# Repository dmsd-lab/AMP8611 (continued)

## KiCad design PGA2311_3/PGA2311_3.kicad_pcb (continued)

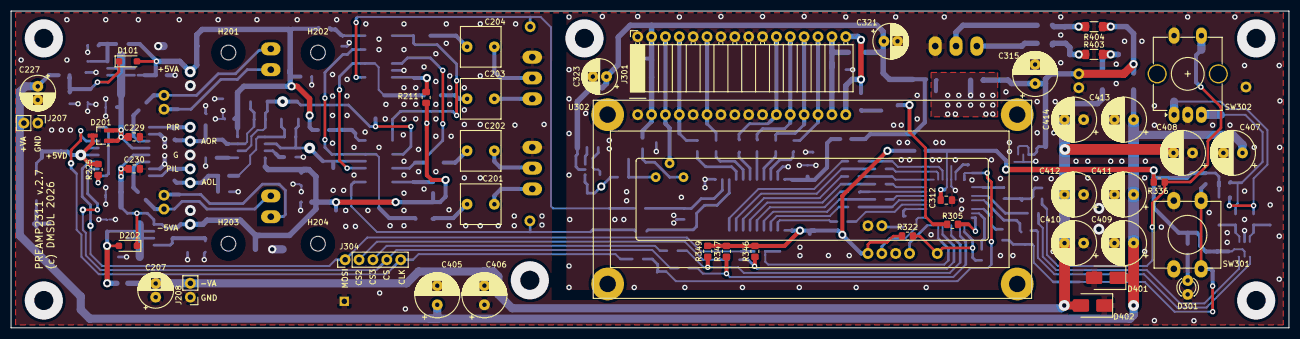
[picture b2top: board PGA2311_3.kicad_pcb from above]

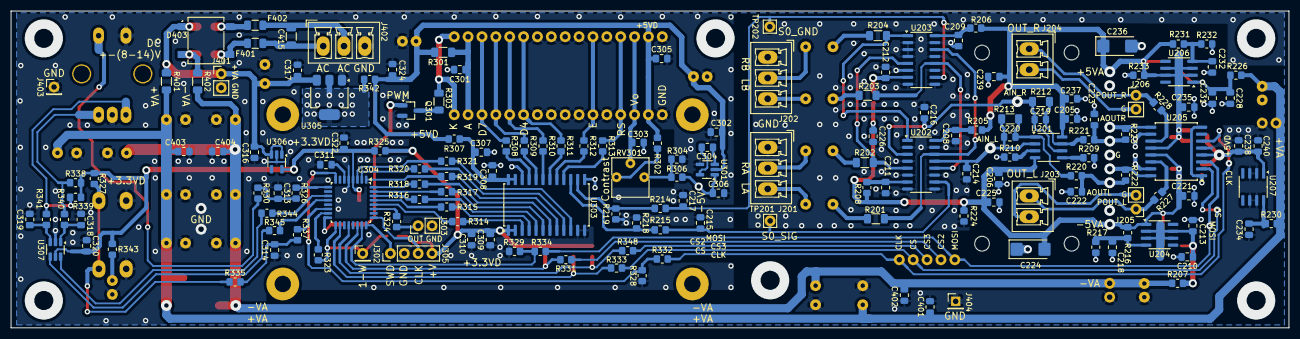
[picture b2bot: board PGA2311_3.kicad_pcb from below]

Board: 2 copper layers, 234.0 x 58.0 mm, 213 parts (164 on the bottom side), 128 nets.

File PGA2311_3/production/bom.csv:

Designator,Footprint,Quantity,Value,LCSC Part #
"C201, C202, C203, C204",C_Rect_L7.2mm_W7.2mm_P5.00mm_FKS2_FKP2_MKS2_MKP2,4,1.5u,
"C205, C206, C208, C209, C211, C212, C221, C225, C226, C229, C230, C235, C237, C238, C239, C303, C309, C310, C311, C312, C313, C314, C318, C319, C320",0805,25,100n,
"C207, C227, C321, C323",CP_Radial_D6.3mm_P2.50mm,4,100u,
"C210, C218, C228, C232, C234, C240, C301, C302, C304, C305, C306, C307, C308, C316, C317, C322, C324, C401, C402, C403, C404",0805,21,10u,
"C213, C214, C216, C231, R207, R222, R223, R226, R230, R304, R325",0805,11,0,
"C215, C217",0805,2,220p,
"C219, C220",0805,2,33p,
"C222, C223",0805,2,1n,
"C224, C236",CP_EIA-6032-20_AVX-F_HandSolder,2,33u,
"C315, C405, C406, C407, C408, C409, C410, C411, C412, C413, C414",CP_Radial_D8.0mm_P3.50mm,11,220u,
C415,1206,1,100n,
"D101, D202",D_SOD-123,2,1N5819,
D201,SOT-23_Handsoldering,1,BAS40-04,
D301,LED_D3.0mm,1,LED_GREEN,
"D401, D402",D_SMB,2,SMAJ15.0A,
D403,Diode_Bridge_OnSemi_SDIP-4L,1,DF01S,
"F401, F402",1206,2,MF-NSMF012-2,
"J201, J202, J402","PhoenixContact_MCV_1,5_3-G-3.81_1x03_P3.81mm_Vertical",3,3,
"J203, J204","PhoenixContact_MCV_1,5_2-G-3.81_1x02_P3.81mm_Vertical",2,2,
"J205, J206, J207, J208",PinHeader_1x02_P2.54mm_Vertical,4,2,
J301,PinSocket_1x16_P2.54mm_Horizontal,1,Conn_01x16,
"J302, J403, J404",PinHeader_1x01_P2.54mm_Vertical,3,1,
J303,PinHeader_1x02_P2.54mm_Vertical,1,Conn_01x02,
J304,PinHeader_1x05_P2.54mm_Vertical,1,4,
J305,PinHeader_1x04_P2.54mm_Vertical,1,4,
J401,PinHeader_1x02_P2.54mm_Vertical,1,1,
Q301,SOT-23_Handsoldering,1,BC817-40,
"R201, R202, R203, R204, R212, R213",1206,6,10k 1%,
"R205, R206, R227, R228, R308, R309, R310, R311, R312, R313, R314, R315, R316, R317, R318, R319, R320, R321",0805,18,100,
"R208, R211",0805,2,10,
"R209, R210",0805,2,5.1k,
"R214, R215, R224, R233, R323, R326, R327, R331, R332, R333, R334, R336, R337, R338, R339, R344, R345, R348",0805,18,1k,
"R216, R231",0805,2,330 1%,
"R217, R232",0805,2,1k 1%,
"R218, R219, R225, R328, R329, R330, R335, R340, R341, R346, R347, R349",0805,12,10k,
"R220, R221, R343",0805,3,220,
"R301, R401, R402",1206,3,1,
"R302, R306",0805,2,2.7k,
R303,1206,1,100,
"R305, R322, R324",0805,3,"2,7k",
"R307, R342",0805,2,0.33,
"R403, R404",1206,2,0,
RV301,Potentiometer_Vishay_T73YP_Vertical,1,KLS4-3362P 5.1k,
SW301,SW_PUSH-12mm,1,SW_Push,
SW302,RotaryEncoder_Alps_EC12E-Switch_Vertical_H20mm_CircularMountingHoles,1,Encoder PEC11R,
"TP201, TP202",TestPoint_THTPad_2.0x2.0mm_Drill1.0mm,2,TestPoint,
U201,SOIC-8_3.9x4.9mm_P1.27mm,1,OPA1678IDR,
"U202, U203",SOIC-16_3.9x9.9mm_P1.27mm,2,CD74HCT4052,
U204,SOIC-8_3.9x4.9mm_P1.27mm,1,LM337LM,
U205,SOIC-16W_7.5x10.3mm_P1.27mm,1,PGA2311UA,
U206,SOIC-8_3.9x4.9mm_P1.27mm,1,LM317LIDR,
U207,SOIC-8_3.9x4.9mm_P1.27mm,1,UA78L05AIDR,
U301,SOT-23-5_HandSoldering,1,TPS60403DBV,
U302,WC1602A,1,WH1602B,
U303,SOIC-24W_7.5x15.4mm_P1.27mm,1,SN74LVC8T245DW,
U304,LQFP-32_7x7mm_P0.8mm,1,STM32G070KBT6,
U305,SOT-223-3_TabPin2,1,TLV1117-50IDC,
U306,SOT-23-5_HandSoldering,1,LP2985-33DBV,
U307,SOT-23-6_Handsoldering,1,SN74LVC2G17DBV,

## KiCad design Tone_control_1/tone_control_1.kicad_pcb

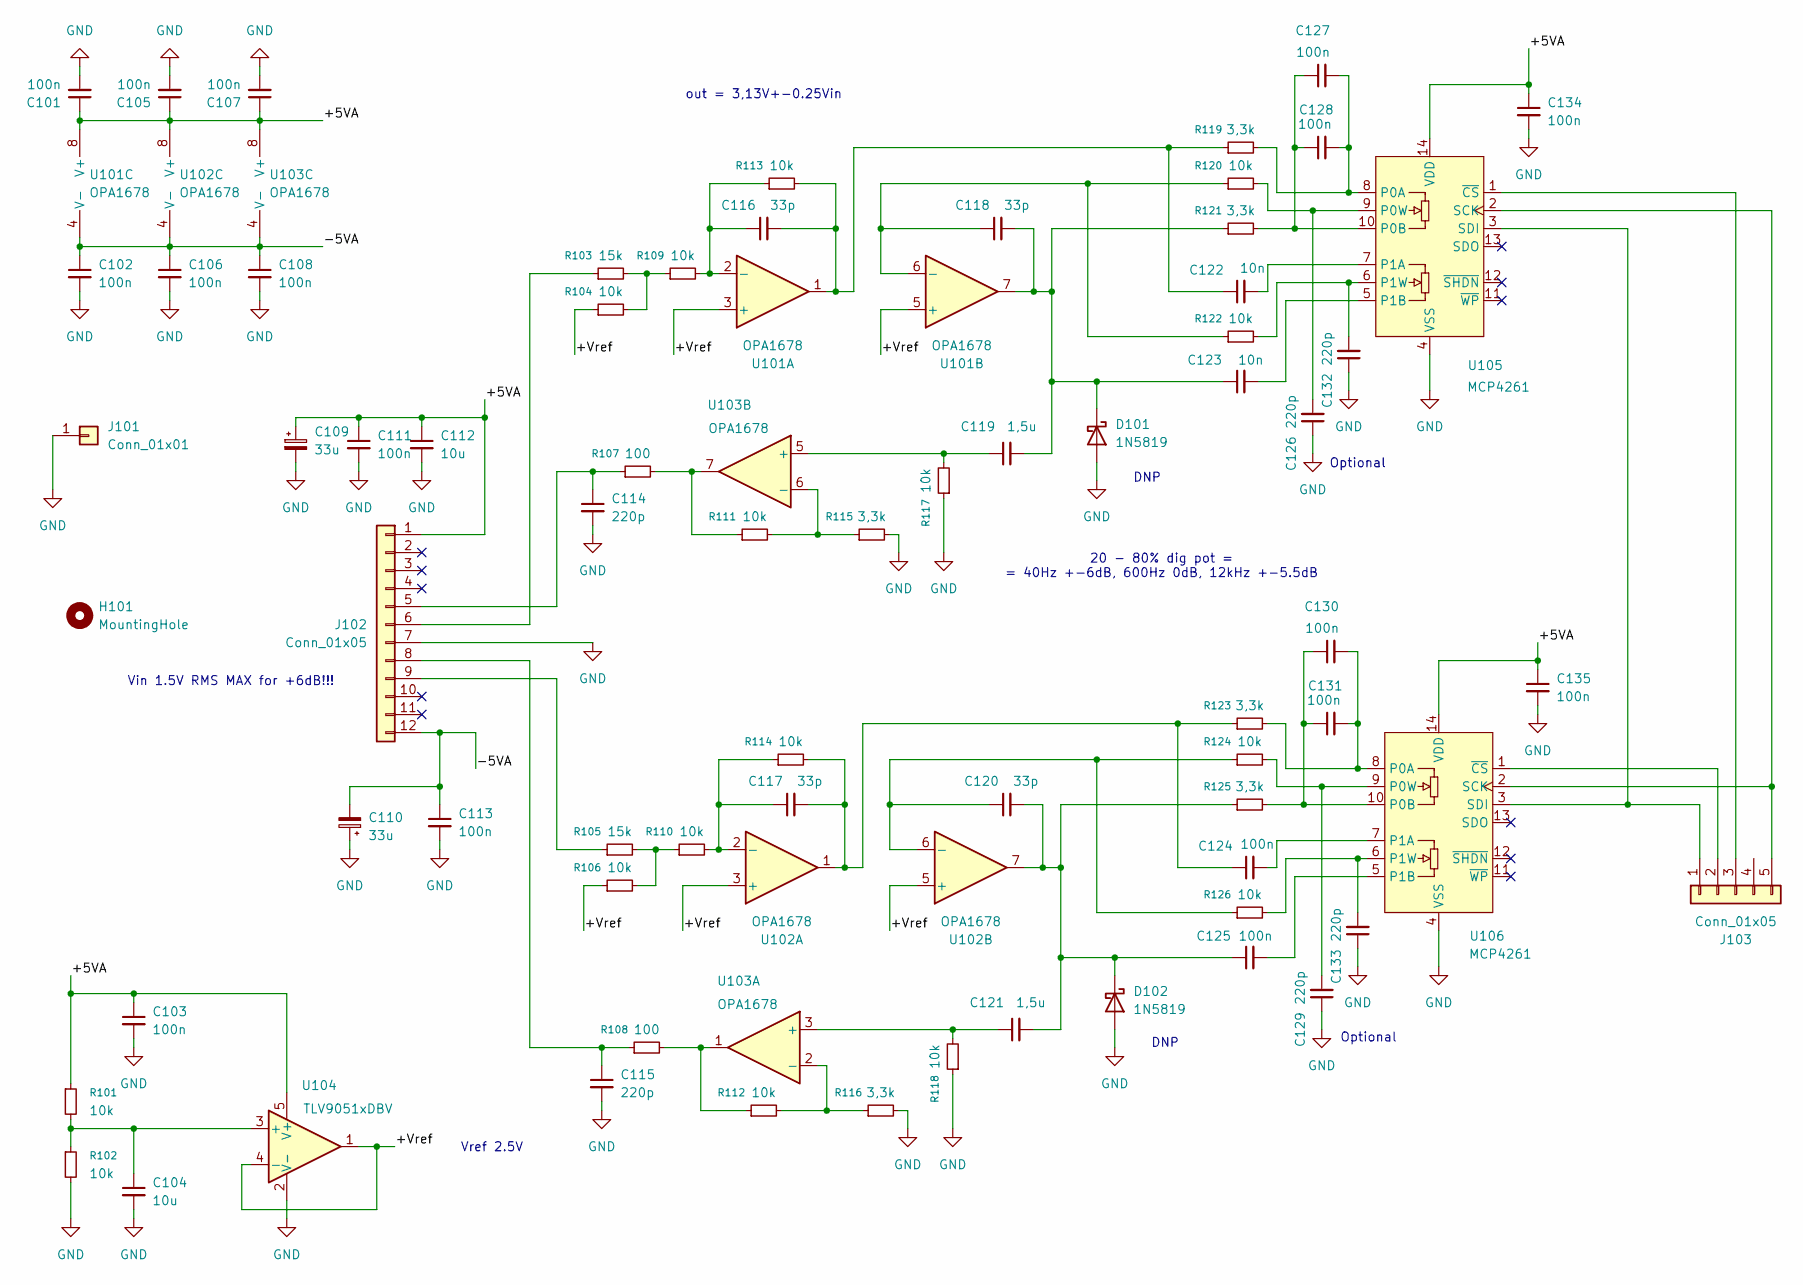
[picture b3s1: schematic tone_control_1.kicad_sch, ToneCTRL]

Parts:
C101, C102, C103, C105, C106, C107, C108, C111, C113, C124, C125, C134, C135: 100n; C_0805_2012Metric_Pad1.18x1.45mm_HandSolder
C104, C112: 10u; C_0805_2012Metric_Pad1.18x1.45mm_HandSolder
C109, C110: 33u; CP_EIA-6032-20_AVX-F_HandSolder
C114, C115, C126, C129, C132, C133: 220p; C_0805_2012Metric_Pad1.18x1.45mm_HandSolder
C116, C117, C118, C120: 33p; C_0805_2012Metric_Pad1.18x1.45mm_HandSolder
C119, C121: 1,5u; C_Rect_L7.5mm_W6.5mm_P5.00mm
C122, C123: 10n; C_0805_2012Metric_Pad1.18x1.45mm_HandSolder
C127, C128, C130, C131: 100n; C_1206_3216Metric_Pad1.33x1.80mm_HandSolder
D101, D102: 1N5819; D_SOD-123
H101: MountingHole; MountingHole_2.7mm_M2.5
J101: Conn_01x01; PinHeader_1x01_P2.54mm_Vertical
J102: Conn_01x05; PinSocket_1x12_P2.54mm_Vertical
J103: Conn_01x05; PinSocket_1x05_P2.54mm_Vertical
R101, R102, R104, R106, R109, R110, R111, R112, R113, R114, R117, R118, R120, R122, R124, R126: 10k; R_0805_2012Metric_Pad1.20x1.40mm_HandSolder
R103, R105: 15k; R_0805_2012Metric_Pad1.20x1.40mm_HandSolder
R107, R108: 100; R_0805_2012Metric_Pad1.20x1.40mm_HandSolder
R115, R116, R119, R121, R123, R125: 3,3k; R_0805_2012Metric_Pad1.20x1.40mm_HandSolder
U101, U102, U103: OPA1678; SOIC-8_3.9x4.9mm_P1.27mm
U104: TLV9051xDBV; SOT-23-5_HandSoldering
U105, U106: MCP4261; TSSOP-14_4.4x5mm_P0.65mm

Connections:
/+5VA: C101.1, C103.1, C105.1, C107.1, C109.1, C111.1, C112.1, C134.1, C135.1, J102.1, R101.1, U101.8 (V+), U102.8 (V+), U103.8 (V+), U104.5 (V+), U105.14 (VDD), U106.14 (VDD)
/+Vref: R104.1, R106.1, U101.3 (+), U101.5 (+), U102.3 (+), U102.5 (+), U104.1, U104.4 (-)
/-5VA: C102.1, C106.1, C108.1, C110.2, C113.1, J102.12, U101.4 (V-), U102.4 (V-), U103.4 (V-)
GND: C101.2, C102.2, C103.2, C104.2, C105.2, C106.2, C107.2, C108.2, C109.2, C110.1, C111.2, C112.2, C113.2, C114.2, C115.2, C126.1, C129.1, C132.1, C133.1, C134.2, C135.2, D101.2 (A), D102.2 (A), J101.1, J102.7, R102.2, R115.2, R116.2, R117.1, R118.1, U104.2 (V-), U105.4 (VSS), U106.4 (VSS)
unnamed: C116.2, C122.1, R113.2, R119.1, U101.1
unnamed: C117.2, C124.1, R114.2, R123.1, U102.1
unnamed: C118.2, C119.2, C123.1, D101.1 (K), R121.1, U101.7
unnamed: C120.2, C121.2, C125.1, D102.1 (K), R125.1, U102.7
unnamed: C114.1, J102.5, R107.1
unnamed: J102.6, R103.1
unnamed: C115.1, J102.8, R108.1
unnamed: J102.9, R105.1
unnamed: J103.1, U105.3 (SDI), U106.3 (SDI)
unnamed: J103.2, U106.1 (~CS)
unnamed: J103.3, U105.1 (~CS)
unnamed: J103.5, U105.2 (SCK), U106.2 (SCK)
unnamed: R103.2, R104.2, R109.1
unnamed: R105.2, R106.2, R110.1
unnamed: R107.2, R111.1, U103.7
unnamed: R108.2, R112.1, U103.1
unnamed: C116.1, R109.2, R113.1, U101.2 (-)
unnamed: C118.1, R120.1, R122.1, U101.6 (-)
unnamed: C117.1, R110.2, R114.1, U102.2 (-)
unnamed: C120.1, R124.1, R126.1, U102.6 (-)
unnamed: C121.1, R118.2, U103.3 (+)
unnamed: R112.2, R116.1, U103.2 (-)
unnamed: C119.1, R117.2, U103.5 (+)
unnamed: R111.2, R115.1, U103.6 (-)
unnamed: C104.1, R101.2, R102.1, U104.3 (+)
unnamed: C127.2, C128.2, R119.2, U105.8 (P0A)
unnamed: C127.1, C128.1, R121.2, U105.10 (P0B)
unnamed: C126.2, R120.2, U105.9 (P0W)
unnamed: C122.2, U105.7 (P1A)
unnamed: C123.2, U105.5 (P1B)
unnamed: C132.2, R122.2, U105.6 (P1W)
unnamed: C130.2, C131.2, R123.2, U106.8 (P0A)
unnamed: C130.1, C131.1, R125.2, U106.10 (P0B)
unnamed: C129.2, R124.2, U106.9 (P0W)
unnamed: C124.2, U106.7 (P1A)
unnamed: C125.2, U106.5 (P1B)
unnamed: C133.2, R126.2, U106.6 (P1W)

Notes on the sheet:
Optional
Vref 2.5V
DNP
20 - 80% dig pot = = 40Hz +-6dB, 600Hz 0dB, 12kHz +-5.5dB
Vin 1.5V RMS MAX for +6dB!!!
out = 3,13V+-0.25Vin

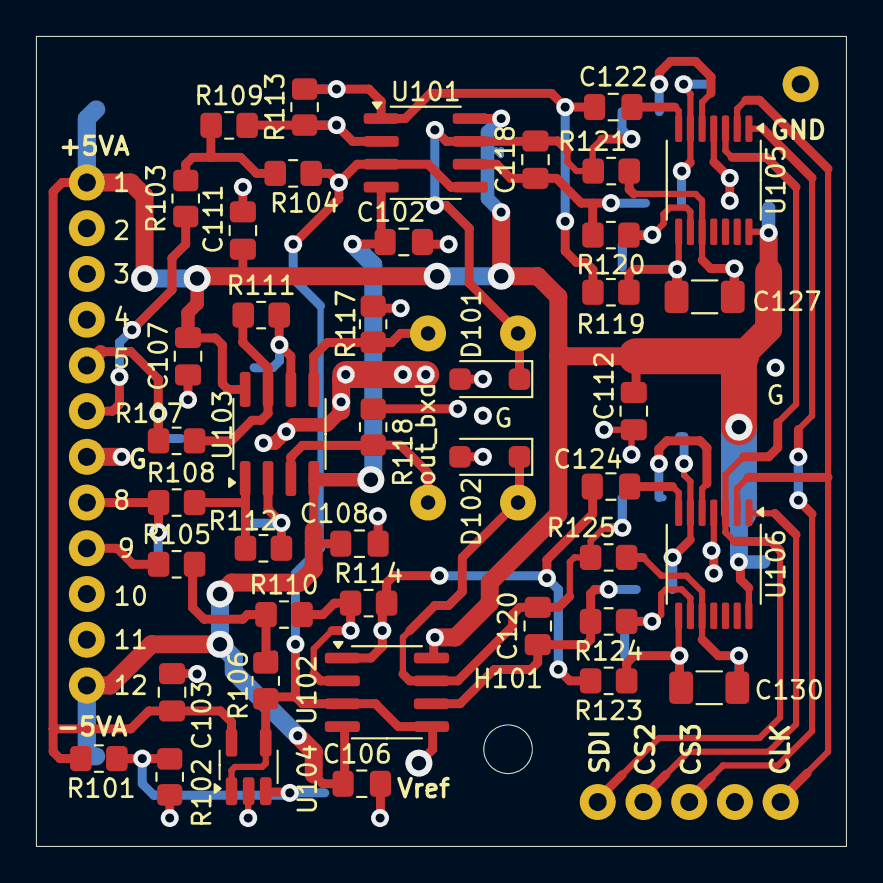
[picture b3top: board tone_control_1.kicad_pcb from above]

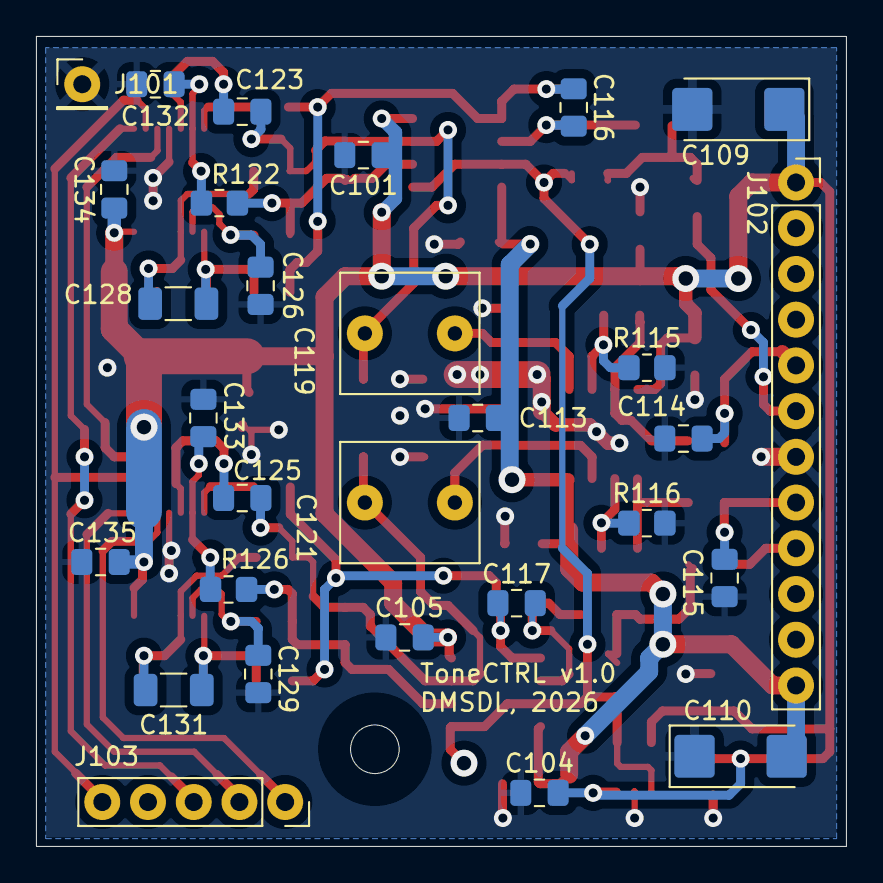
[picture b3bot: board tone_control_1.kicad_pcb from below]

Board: 2 copper layers, 45.0 x 45.0 mm, 73 parts (29 on the bottom side), 41 nets.

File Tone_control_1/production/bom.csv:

Designator,Footprint,Quantity,Value,LCSC Part #
"C101, C102, C103, C105, C106, C107, C108, C111, C113, C124, C125, C134, C135",0805,13,100n,
"C104, C112",0805,2,10u,
"C109, C110",CP_EIA-6032-20_AVX-F_HandSolder,2,33u,
"C114, C115, C126, C129, C132, C133",0805,6,220p,
"C116, C117, C118, C120",0805,4,33p,
"C119, C121",C_Rect_L7.5mm_W6.5mm_P5.00mm,2,"1,5u",
"C122, C123",0805,2,10n,
"C127, C128, C130, C131",1206,4,100n,
"D101, D102",D_SOD-123,2,1N5819,
J101,PinHeader_1x01_P2.54mm_Vertical,1,Conn_01x01,
J102,PinSocket_1x12_P2.54mm_Vertical,1,Conn_01x05,
J103,PinSocket_1x05_P2.54mm_Vertical,1,Conn_01x05,
"R101, R102, R104, R106, R109, R110, R111, R112, R113, R114, R117, R118, R120, R122, R124, R126",0805,16,10k,
"R103, R105",0805,2,15k,
"R107, R108",0805,2,100,
"R115, R116, R119, R121, R123, R125",0805,6,"3,3k",
"U101, U102, U103",SOIC-8_3.9x4.9mm_P1.27mm,3,OPA1678,
U104,SOT-23-5_HandSoldering,1,TLV9051xDBV,
"U105, U106",TSSOP-14_4.4x5mm_P0.65mm,2,MCP4261,
